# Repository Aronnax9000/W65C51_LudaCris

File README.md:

# W65C51_LudaCris
A hardware workaround for the W65C51 Transmit Data Register Empty (TDRE) Bug

The W65C51N Asynchronous Communications Interface Adapter (ACIA) [datasheet](https://www.westerndesigncenter.com/wdc/documentation/w65c51n.pdf) is a 28-pin UART designed and produced by the Western Design Center.

Like all UARTs, the ACIA's primary function is to provide an interface between a parallel data bus (8 bits wide for the ACIA, with additional lines for chip and I/O register selection) and a serial data connection, under the supervision of a Central Processing Unit ("CPU", or "processor"). Bits are transmitted or received according to a set of possible serial line disciplines, which latter are pre-programmed into the ACIA by the processor. The design allows choice of baud rate, word length, number of stop bits, and parity checking. A design flaw means that in practice, parity checking is not available for either transmission or reception.

The ACIA features a baud rate generator capable of transmitting and receiving at one of 16 configurable standard baud rates, when supplied with an external crystal or (typically crystal-based) oscillator circuit as a time base. The baud rate generator divides the pulses from the externally supplied time base by the appropriate integer divisor to achieve the programmed baud rate. In support of traditional baud rates found in industry, the nominal oscillator frequency is at 1.8432 MHz (the "standard frequency" 

Here is a table of the standard baud rates supported by the ACIA driven by the standard frequency of 1.8432 MHz. Bits 3 to 0 of the Control Register are given, followed by the target baud rate, followed by the necessary integer divisor represented in decimal, and as a 16 bit integer.

Ctrl   Baud   Baud Rate Divisor Table
3210   Rate   Div 15     8 7      0 
---- ------ ----- -------- --------
0000 115200    16 00000000 00010000
0001     50 36864 10010000 00000000
0010     75 24576 01100000 00000000
0011 109.92 16769 01000001 10000001
0100 134.51 13704 00110101 10001000
0101    150 12288 00110000 00000000
0110    300  6144 00011000 00000000
0111    600  3072 00001100 00000000
1000   1200  1536 00000110 00000000
1001   1800  1024 00000100 00000000
1010   2400   768 00000011 00000000
1011   3600   512 00000010 00000000
1100   4800   384 00000001 10000000
1101   7200   256 00000001 00000000
1110   9600   192 00000000 11000000
1111  19200    96 00000000 01100000

Each of the 16 bits of each 16-bit divisor is active (1) for a subset of the 16 available baud rates. If the bits of the divsor are assigned the names Q15 to Q0, each bit should be a 1 if and only if the following choices of baud rate are selected. The second column consolidates similar input values by specifying X ("Don't Care") in bit positions which may be ignored.

;Table of Divisor Bits per Control Register Value
;X = Don't Care
;Quot Baud Rate Selections    
;Bit  3210 Control Register
;Q15  0001                     = 0001
;Q14  0010 0011                = 001X
;Q13  0010 0100 0101           = 0010 010X
;Q12  0001 0100 0101 0110      = 0X01 01X0
;Q11  0110 0111                = 011X
;Q10  0100 0111 1000 1001      = 0100 0111 100X
;Q9   1000 1010 1011           = 1000 101X
;Q8   0011 0100 1010 1100 1101 = 0011 0100 1010 110X
;Q7   0011 0100 1100 1110      = 0011 0100 11X0
;Q6   1110 1111                = 111X
;Q5   1111                     = 1111
;Q4   0000                     = 0000
;Q3   0100                     = 0100
;Q2   (none, always 0)         = Not mapped by PLD
;Q1   (none, always 0)         = Not mapped by PLD
;Q0   0011                     = 0011

Additional bits in the ACIA Control Register control the remaining features of serial line discipline supported by the ACIA, namely, word length (5, 6, 7, or 8 bits) and number of stop bits (1, 2, and in the exceptional case of 5 bit word length, 1.5 bits).

A start bit is always transmitted. Word length is selectable from lengths between 5 to 8 bits, as is the number of stop bits (1, 2, or, for 5 bit word length, 1.5 stop bits).

Transmission Unit Sizes (7-11 bits, 1.5 stop bits = 2 stop bits.)

Ctl
Bit Start   Word Stop Ceil
765  Bits Length Bits Total
--- ----- ------ ---- -----
000     1      8    1    10
001     1      7    1     9
010     1      6    1     8
011     1      5    1     7
100     1      8    2    11
101     1      7    2    10
110     1      6    2     9
111     1      5  1.5     8

Limitations of the W65C51N

The W65C51N has a number of well-documented limitations stemming from design defects that are unlikely ever to be fixed. Chief among these limitations are the following:

* Transmitter Data Register Empty (TDRE) bug. Status Register bit 4, per the original design, can be used to poll the transmit buffer to determine if the most recent transmission unit has completed transmission. This feature does not work in production W65C51N units. Additionally, bits 2-3 of the Command Register (Transmitter Interrupt Control (TIC)), which in the design were used to control whether interrupts were generated on transitions of the Transmitter Data Register Empty (TDRE) Status Register bit, do not meaningfully enable interrupts, as the TDRE never transitions.

* No parity. The W65C51N does not generate or consume parity bits. The original settings for selecting parity in line discipline are. Within the original design, Status Register Bit 0 was allocated to represent the state of the parity check of the most recently received transmission unit. In production, this bit's value must be ignored. Additionally, bits 6-7 of the Command Register were, according to the original design, allocated to control the selection of parity mode: these bits are ignored in production.

Of these two limitations, the latter (lack of parity bit line discipline) is less problematic, as much serial hardware can cope with using no parity. The other limitation, that of the Transmit Data Register Empty (TDRE) bug, prevents the processor from learning, either by interrupt or by active polling of the Status Register, when transmission has concluded. 

The W65C51N datasheet recommends a software workaround for the TDRE bug, namely, that transmission code enter a loop after the transmission of each byte, in an attempt to ensure that sufficient time elapses before the processor attempts to send the next byte. This workaround wasteful of processor cycles. Additionally, since the time required for transmission is variable in baud rate and transmission unit length, and dependent on a different time base than the clock cycle of the typical processor, naive implementations of software delay loops run the risk of not waiting long enough, or wasting processor cycles. 

A better workaround would be hardware based. Fortunately, the W65C51N exposes an active low input, Data Set Ready, (DSRB) which is exposed via the Status Register. Data Set Ready is part of the RS-232 serial standard, indicating that the transmission equipment (typically, a modem) is ready (logic level low) or not ready (logic level high).

Further, the ACIA can be configured to assert an interrupt to the processor on a change of state of DSRB. 

The present design seeks to overcome the TDRE bug by functionally replicating the W65C51N's baud rate generator using a cascading series of binary counters, programmed to count pulses from the external clock source supplied to the ACIA. 

Since word length is variable, the generated baud clock is used to increment an additional binary counter, programmed with the length, in bits, of the ACIA's configured transmission unit size of between 7-11 bits.

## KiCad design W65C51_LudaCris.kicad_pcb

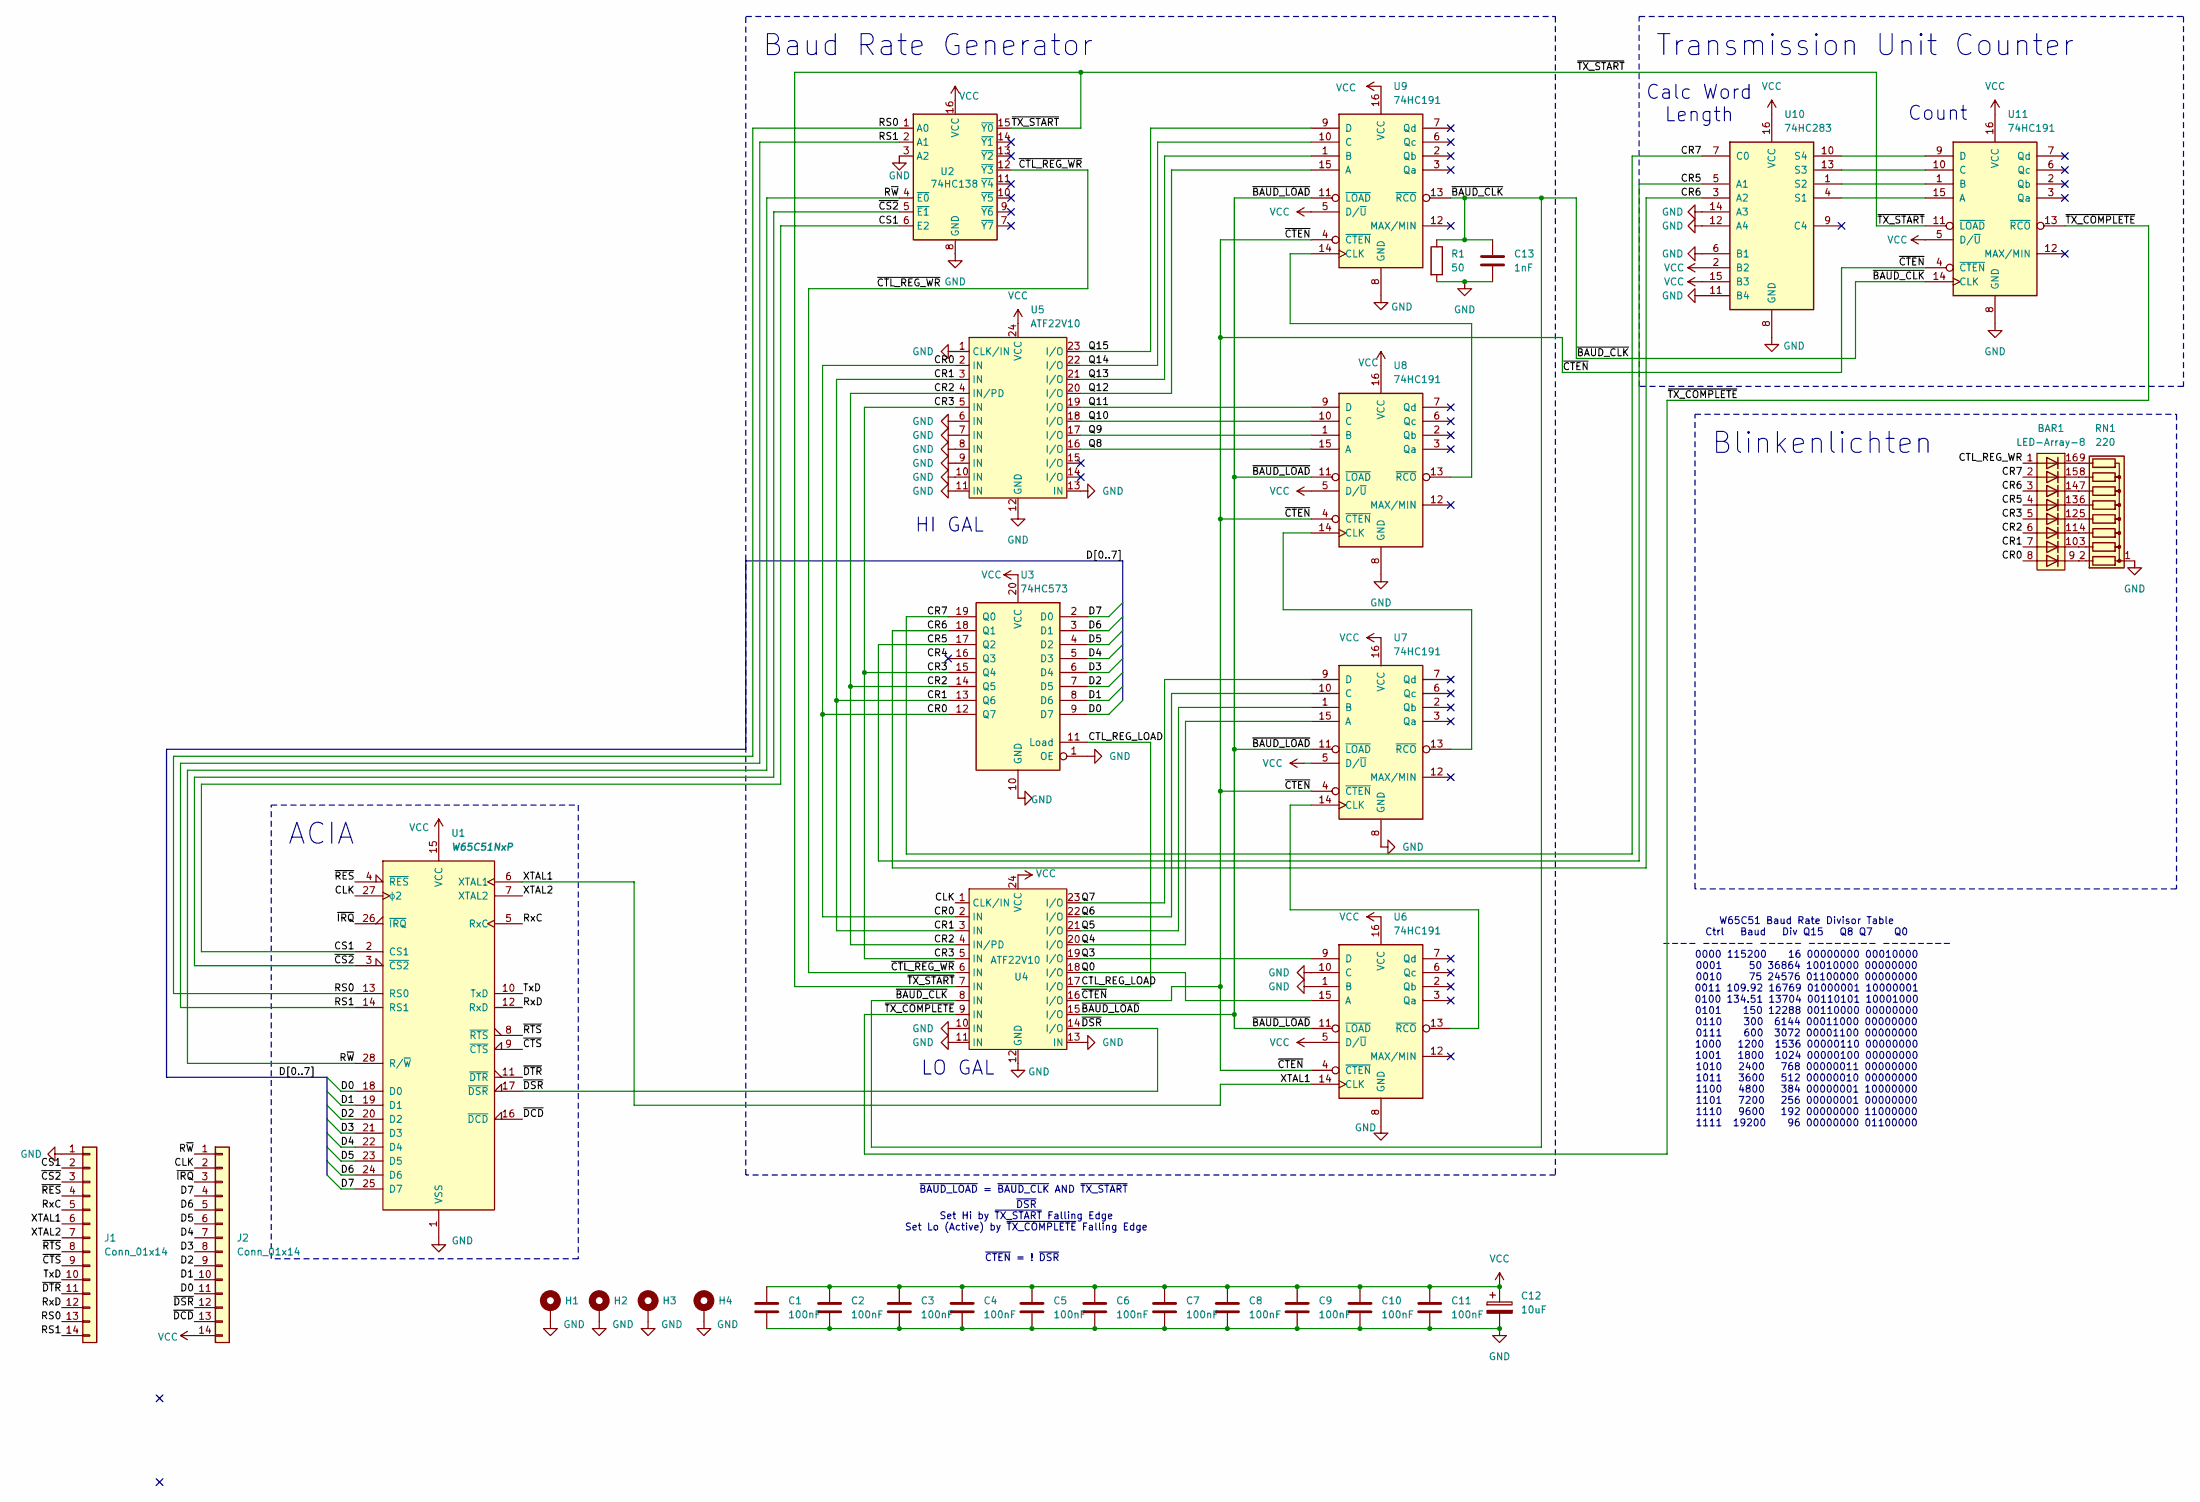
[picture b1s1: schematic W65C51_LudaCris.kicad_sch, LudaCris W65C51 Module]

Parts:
BAR1: LED-Array-8; DIP-16_W7.62mm_Socket
C1, C2, C3, C4, C5, C6, C7, C8, C9, C10, C11: 100nF; C_Disc_D3.4mm_W2.1mm_P2.50mm
C12: 10uF; CP_Radial_D4.0mm_P1.50mm
C13: 1nF; C_Disc_D3.4mm_W2.1mm_P2.50mm
H1, H2, H3, H4: MountingHole_Pad; MountingHole_3.2mm_M3_Pad
J1, J2: Conn_01x14; PinHeader_1x14_P2.54mm_Vertical
R1: 50; R_Axial_DIN0207_L6.3mm_D2.5mm_P7.62mm_Horizontal
RN1: 220; R_Array_SIP9
U1: W65C51NxP; DIP-28_W15.24mm_Socket
U2: 74HC138; DIP-16_W7.62mm_Socket
U3: 74HC573; DIP-20_W7.62mm_Socket
U4, U5: ATF22V10; DIP-24_W7.62mm_Socket
U6, U7, U8, U9, U11: 74HC191; DIP-16_W7.62mm_Socket
U10: 74HC283; DIP-16_W7.62mm_Socket

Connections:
/CLK: J2.2, U1.27 (ϕ2), U4.1 (CLK/IN)
/CR0: BAR1.8 (A), U3.12 (Q7), U4.2 (IN), U5.2 (IN)
/CR1: BAR1.7 (A), U3.13 (Q6), U4.3 (IN), U5.3 (IN)
/CR2: BAR1.6 (A), U3.14 (Q5), U4.4 (IN/PD), U5.4 (IN/PD)
/CR3: BAR1.5 (A), U3.15 (Q4), U4.5 (IN), U5.5 (IN)
/CR4: U3.16 (Q3)
/CR5: BAR1.4 (A), U3.17 (Q2), U10.5 (A1)
/CR6: BAR1.3 (A), U3.18 (Q1), U10.3 (A2)
/CR7: BAR1.2 (A), U3.19 (Q0), U10.7 (C0)
/CS1: J1.2, U1.2 (CS1), U2.6 (E2)
/CTL_REG_LOAD: U3.11 (Load), U4.17 (I/O)
/D0: J2.11, U1.18 (D0), U3.9 (D7)
/D1: J2.10, U1.19 (D1), U3.8 (D6)
/D2: J2.9, U1.20 (D2), U3.7 (D5)
/D3: J2.8, U1.21 (D3), U3.6 (D4)
/D4: J2.7, U1.22 (D4), U3.5 (D3)
/D5: J2.6, U1.23 (D5), U3.4 (D2)
/D6: J2.5, U1.24 (D6), U3.3 (D1)
/D7: J2.4, U1.25 (D7), U3.2 (D0)
/Q0: U4.18 (I/O), U6.15 (A)
/Q3: U4.19 (I/O), U6.9 (D)
/Q4: U4.20 (I/O), U7.15 (A)
/Q5: U4.21 (I/O), U7.1 (B)
/Q6: U4.22 (I/O), U7.10 (C)
/Q7: U4.23 (I/O), U7.9 (D)
/Q8: U5.16 (I/O), U8.15 (A)
/Q9: U5.17 (I/O), U8.1 (B)
/Q10: U5.18 (I/O), U8.10 (C)
/Q11: U5.19 (I/O), U8.9 (D)
/Q12: U5.20 (I/O), U9.15 (A)
/Q13: U5.21 (I/O), U9.1 (B)
/Q14: U5.22 (I/O), U9.10 (C)
/Q15: U5.23 (I/O), U9.9 (D)
/RS0: J1.13, U1.13 (RS0), U2.1 (A0)
/RS1: J1.14, U1.14 (RS1), U2.2 (A1)
/RxC: J1.5, U1.5 (RxC)
/RxD: J1.12, U1.12 (RxD)
/R~W: J2.1, U1.28 (R/~W), U2.4 (~E0)
/TxD: J1.10, U1.10 (TxD)
/XTAL1: J1.6, U1.6 (XTAL1), U6.14 (CLK)
/XTAL2: J1.7, U1.7 (XTAL2)
/~BAUD_CLK: C13.1, R1.1, U4.8 (IN), U9.13 (~RCO), U11.14 (CLK)
/~BAUD_LOAD: U4.15 (I/O), U6.11 (~LOAD), U7.11 (~LOAD), U8.11 (~LOAD), U9.11 (~LOAD)
/~CS2: J1.3, U1.3 (~CS2), U2.5 (~E1)
/~CTEN: U4.16 (I/O), U6.4 (~CTEN), U7.4 (~CTEN), U8.4 (~CTEN), U9.4 (~CTEN), U11.4 (~CTEN)
/~CTL_REG_WR: U2.12 (~Y3), U4.6 (IN)
/~CTS: J1.9, U1.9 (~CTS)
/~DCD: J2.13, U1.16 (~DCD)
/~DSR: J2.12, U1.17 (~DSR), U4.14 (I/O)
/~DTR: J1.11, U1.11 (~DTR)
/~IRQ: J2.3, U1.26 (~IRQ)
/~RES: J1.4, U1.4 (~RES)
/~RTS: J1.8, U1.8 (~RTS)
/~TX_COMPLETE: U4.9 (IN), U11.13 (~RCO)
/~TX_START: U2.15 (~Y0), U4.7 (IN), U11.11 (~LOAD)
GND: C1.2, C2.2, C3.2, C4.2, C5.2, C6.2, C7.2, C8.2, C9.2, C10.2, C11.2, C12.2, C13.2, H1.1, H2.1, H3.1, H4.1, J1.1, R1.2, RN1.1 (common), U1.1 (VSS), U2.3 (A2), U2.8 (GND), U3.1 (OE), U3.10 (GND), U4.10 (IN), U4.11 (IN), U4.12 (GND), U4.13 (IN), U5.1 (CLK/IN), U5.6 (IN), U5.7 (IN), U5.8 (IN), U5.9 (IN), U5.10 (IN), U5.11 (IN), U5.12 (GND), U5.13 (IN), U6.1 (B), U6.8 (GND), U6.10 (C), U7.8 (GND), U8.8 (GND), U9.8 (GND), U10.6 (B1), U10.8 (GND), U10.11 (B4), U10.12 (A4), U10.14 (A3), U11.8 (GND)
unnamed: BAR1.9 (K), RN1.2 (R1)
unnamed: BAR1.10 (K), RN1.3 (R2)
unnamed: BAR1.11 (K), RN1.4 (R3)
unnamed: BAR1.12 (K), RN1.5 (R4)
unnamed: BAR1.13 (K), RN1.6 (R5)
unnamed: BAR1.14 (K), RN1.7 (R6)
unnamed: BAR1.15 (K), RN1.8 (R7)
unnamed: BAR1.16 (K), RN1.9 (R8)
unnamed: U6.13 (~RCO), U7.14 (CLK)
unnamed: U7.13 (~RCO), U8.14 (CLK)
unnamed: U8.13 (~RCO), U9.14 (CLK)
unnamed: U10.4 (S1), U11.15 (A)
unnamed: U10.1 (S2), U11.1 (B)
unnamed: U10.13 (S3), U11.10 (C)
unnamed: U10.10 (S4), U11.9 (D)
VCC: C1.1, C2.1, C3.1, C4.1, C5.1, C6.1, C7.1, C8.1, C9.1, C10.1, C11.1, C12.1, J2.14, U1.15 (VCC), U2.16 (VCC), U3.20 (VCC), U4.24 (VCC), U5.24 (VCC), U6.5 (D/~U), U6.16 (VCC), U7.5 (D/~U), U7.16 (VCC), U8.5 (D/~U), U8.16 (VCC), U9.5 (D/~U), U9.16 (VCC), U10.2 (B2), U10.15 (B3), U10.16 (VCC), U11.5 (D/~U), U11.16 (VCC)

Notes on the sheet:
ACIA
Blinkenlichten
Transmission Unit Counter
Baud Rate Generator
~{DSR} Set Hi by ~{TX_START} Falling Edge Set Lo (Active) by ~{TX_COMPLETE} Falling Edge
Calc Word Length
W65C51 Baud Rate Divisor Table Ctrl Baud Div Q15 Q8 Q7 Q0 ---- ------ ----- -------- -------- 0000 115200 16 00000000 00010000 0001 50 36864 10010000 00000000 0010 75 24576 01100000 00000000 0011 109.92 16769 01000001 10000001 0100 134.51 13704 00110101 10001000 0101 150 12288 00110000 00000000 011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
LO GAL
~{CTEN} = ! ~{DSR}
Count
HI GAL
~{BAUD_LOAD} = ~{BAUD_CLK} AND ~{TX_START}

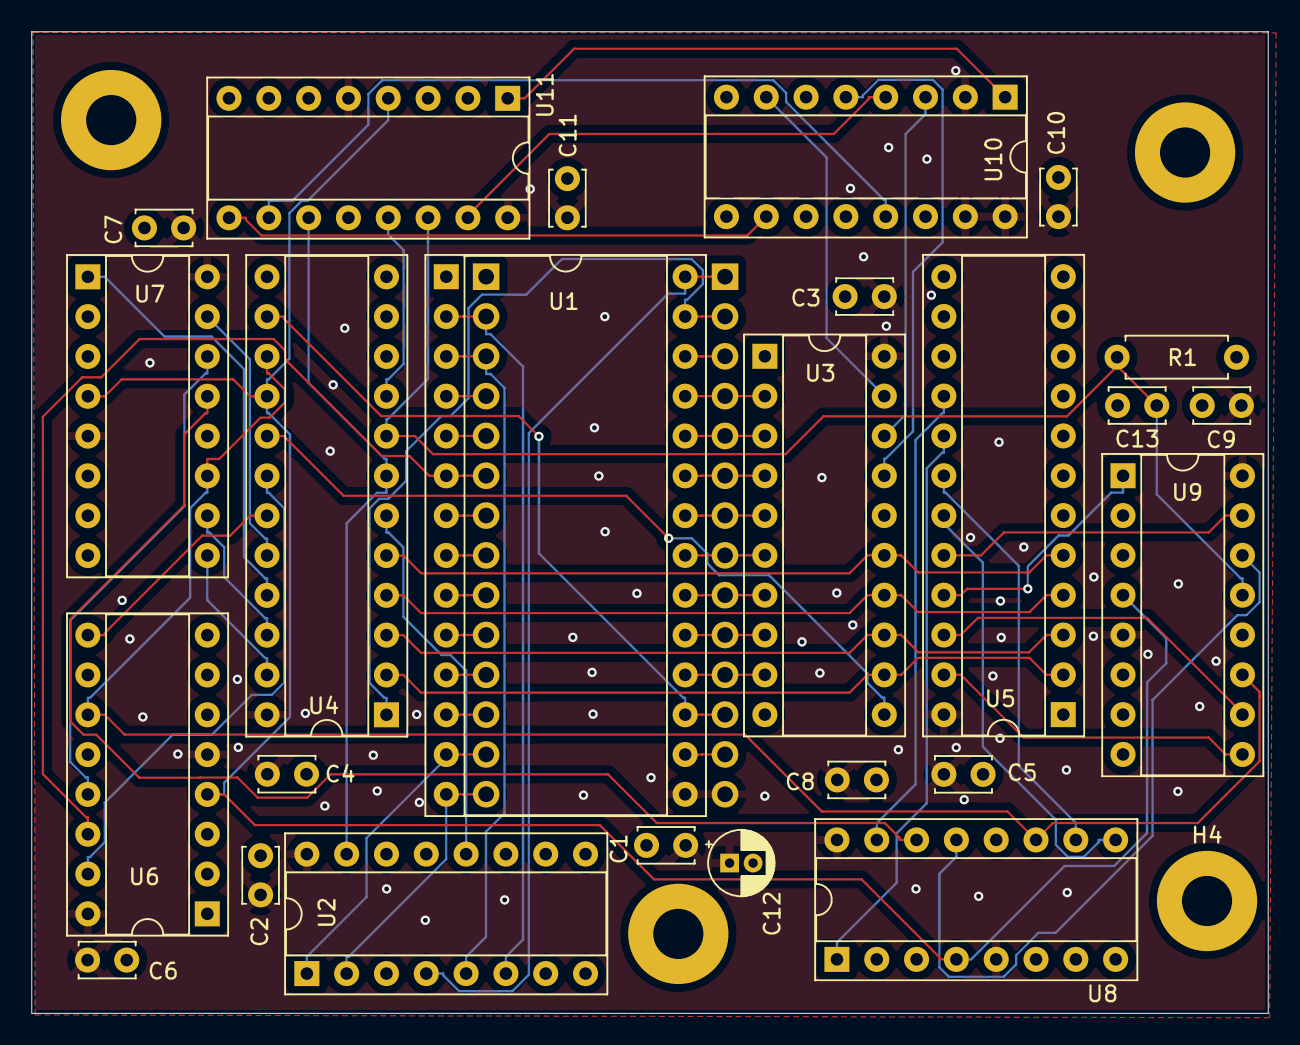
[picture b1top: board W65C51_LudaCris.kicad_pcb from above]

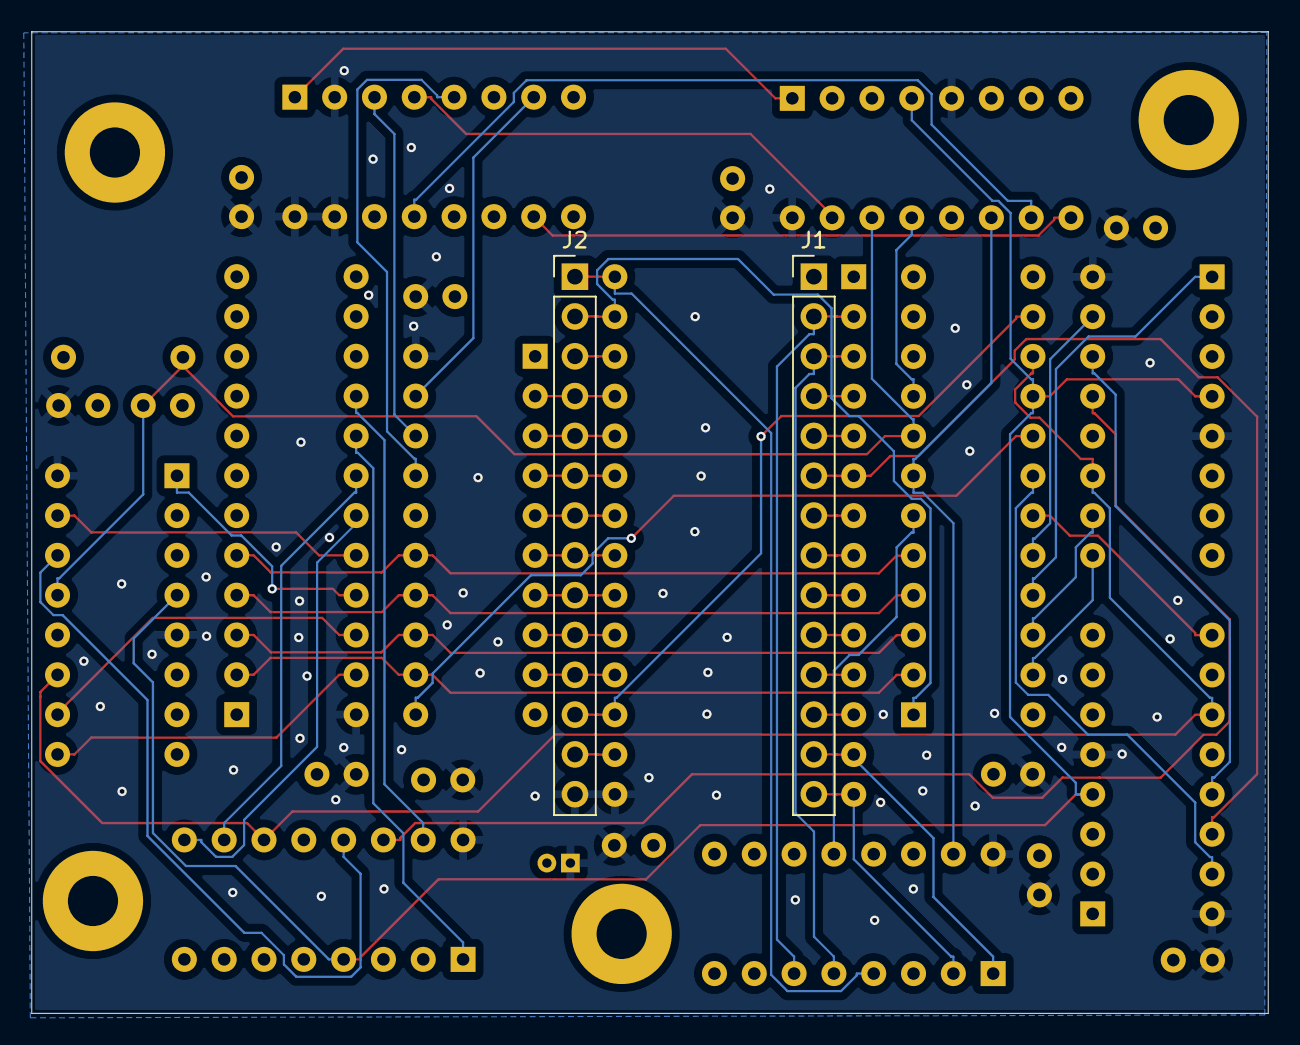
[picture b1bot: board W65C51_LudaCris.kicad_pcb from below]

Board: 4 copper layers, 78.9 x 62.6 mm, 31 parts (2 on the bottom side), 63 nets.

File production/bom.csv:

Designator,Footprint,Quantity,Value,LCSC Part #
"C1, C10, C11, C2, C3, C4, C5, C6, C7, C8, C9",C_Disc_D3.4mm_W2.1mm_P2.50mm,11,100nF,
C12,CP_Radial_D4.0mm_P1.50mm,1,10uF,
C13,C_Disc_D3.4mm_W2.1mm_P2.50mm,1,1nF,
"H1, H2, H3, H4",MountingHole_3.2mm_M3_Pad,4,MountingHole_Pad,
"J1, J2",PinHeader_1x14_P2.54mm_Vertical,2,Conn_01x14,
R1,R_Axial_DIN0207_L6.3mm_D2.5mm_P7.62mm_Horizontal,1,50,
U1,DIP-28_W15.24mm_Socket,1,W65C51NxP,
U10,DIP-16_W7.62mm_Socket,1,74HC283,
"U11, U6, U7, U8, U9",DIP-16_W7.62mm_Socket,5,74HC191,
U2,DIP-16_W7.62mm_Socket,1,74HC138,
U3,DIP-20_W7.62mm_Socket,1,74HC573,
"U4, U5",DIP-24_W7.62mm_Socket,2,ATF22V10,

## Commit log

2024-03-21 Finish
2024-03-23 StartofPCB
2024-03-25 GAL PLD
2024-03-25 More PLD
2024-03-29 PCB 2.54mm centres
